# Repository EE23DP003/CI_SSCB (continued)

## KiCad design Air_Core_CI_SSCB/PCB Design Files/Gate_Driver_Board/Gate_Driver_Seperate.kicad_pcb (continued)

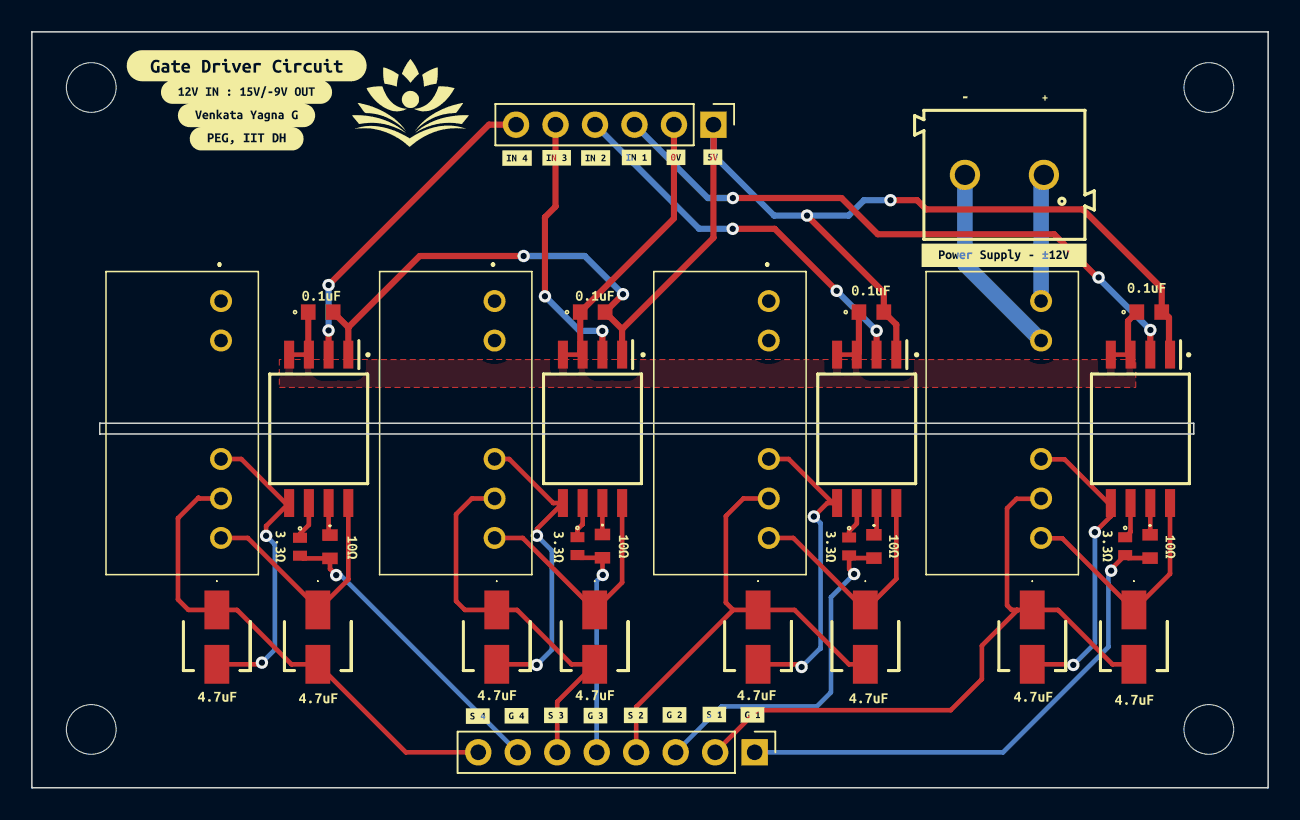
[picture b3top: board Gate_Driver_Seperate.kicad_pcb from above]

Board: 2 copper layers, 79.5 x 48.6 mm, 80 parts (0 on the bottom side), 32 nets.

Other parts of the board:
kibuzzard-6538B5CC: G***; kibuzzard-6538B5CC
kibuzzard-6538C0C5: G***; kibuzzard-6538C0C5
kibuzzard-6538C1AB, kibuzzard-6538C1AB#2, kibuzzard-6538C1AB#3, kibuzzard-6538C1AB#4: G***; kibuzzard-6538C1AB
kibuzzard-6538C1B4, kibuzzard-6538C1B4#2, kibuzzard-6538C1B4#3, kibuzzard-6538C1B4#4: G***; kibuzzard-6538C1B4
kibuzzard-6538C1BA, kibuzzard-6538C1BA#2, kibuzzard-6538C1BA#3, kibuzzard-6538C1BA#4, kibuzzard-6538C1BA#5, kibuzzard-6538C1BA#6, kibuzzard-6538C1BA#7, kibuzzard-6538C1BA#8: G***; kibuzzard-6538C1BA
kibuzzard-6538C1C8: G***; kibuzzard-6538C1C8
kibuzzard-6538C1CF: G***; kibuzzard-6538C1CF
kibuzzard-6538C2A7: G***; kibuzzard-6538C2A7
kibuzzard-6538C2B9: G***; kibuzzard-6538C2B9
kibuzzard-6538C2CF: G***; kibuzzard-6538C2CF
kibuzzard-6538C2DE: G***; kibuzzard-6538C2DE
kibuzzard-6538C2F6: G***; kibuzzard-6538C2F6
kibuzzard-6538C23E: G***; kibuzzard-6538C23E
kibuzzard-6538C25C: G***; kibuzzard-6538C25C
kibuzzard-6538C26B: G***; kibuzzard-6538C26B
kibuzzard-6538C30F: G***; kibuzzard-6538C30F
kibuzzard-6538C035: G***; kibuzzard-6538C035
kibuzzard-6538C37E, kibuzzard-6538C37E#2, kibuzzard-6538C37E#3, kibuzzard-6538C37E#4: G***; kibuzzard-6538C37E
kibuzzard-6538C041: G***; kibuzzard-6538C041
kibuzzard-6538C42C: G***; kibuzzard-6538C42C
kibuzzard-6538C049: G***; kibuzzard-6538C049
kibuzzard-6538C053: G***; kibuzzard-6538C053
kibuzzard-6538C196: G***; kibuzzard-6538C196
kibuzzard-6538C287: G***; kibuzzard-6538C287
kibuzzard-6538C299: G***; kibuzzard-6538C299
kibuzzard-6538C318: G***; kibuzzard-6538C318
kibuzzard-6538C335: G***; kibuzzard-6538C335
kibuzzard-6541E0B2: G***; kibuzzard-6541E0B2
kibuzzard-654732F0: G***; kibuzzard-654732F0

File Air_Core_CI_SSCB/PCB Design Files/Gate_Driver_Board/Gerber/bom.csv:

Designator,Footprint,Quantity,Value,LCSC Part #
"C1, C10, C4, C7",C0603,4,C0603C104K3PACTU,
"C11, C12, C2, C3, C5, C6, C8, C9",EEE1AA220WR,8,EEE1HA4R7WAR,
"H1, H2, H3, H4",MountingHole_3.2mm_M3,4,MountingHole,
"IC1, IC2, IC3, IC4",SOIC127P1030X265-8N,4,1ED3122MU12HXUMA1,
J1,691213510002,1,691213510002,
J2,PinHeader_1x06_P2.54mm_Vertical,1,Conn_01x06_Pin,
J3,PinHeader_1x08_P2.54mm_Vertical,1,Conn_01x08_Pin,
"PS1, PS2, PS3, PS4",R12P21503D,4,R12P21503D,
"R1, R3, R5, R7",RCS0603_E3,4,RCS060310R0JNEA,
"R2, R4, R6, R8",ERJUP3,4,ERJ-UP3J3R3V,

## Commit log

2025-10-06 Design files added
2025-10-06 updated design files
